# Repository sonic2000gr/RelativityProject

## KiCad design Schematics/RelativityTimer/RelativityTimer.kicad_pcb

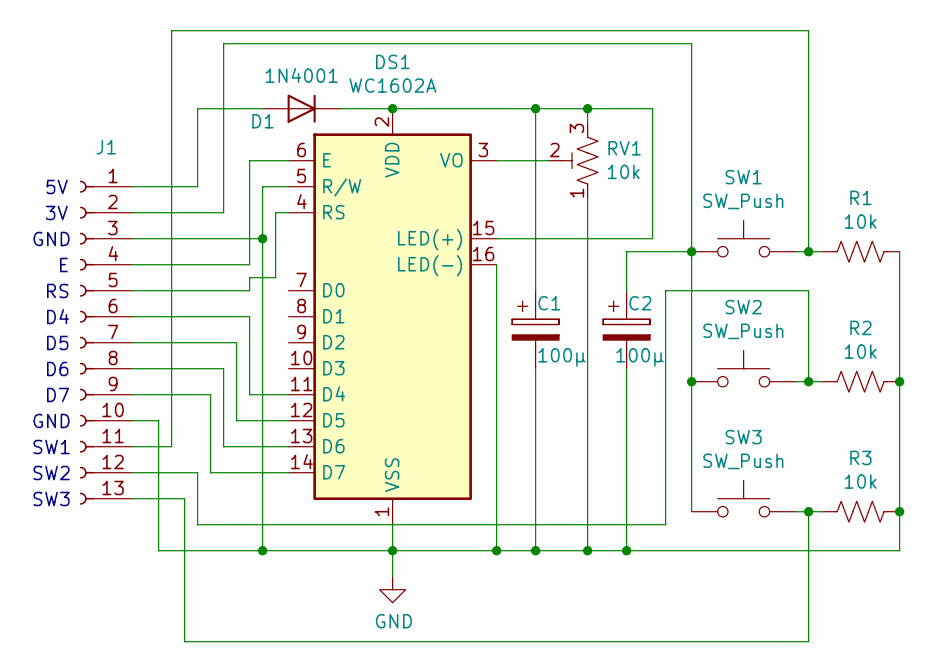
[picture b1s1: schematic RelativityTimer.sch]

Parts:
C1, C2: 100μ; CP_Radial_D8.0mm_P3.50mm
D1: 1N4001; D_DO-41_SOD81_P10.16mm_Horizontal
DS1: WC1602A
J1: Conn_01x12_Female; PinHeader_1x13_P2.54mm_Vertical
R1, R2, R3: 10k; R_Axial_DIN0207_L6.3mm_D2.5mm_P10.16mm_Horizontal
RV1: 10k; Potentiometer_ACP_CA9-H2,5_Horizontal
SW1, SW2, SW3: SW_Push; SW_PUSH_6mm_H4.3mm

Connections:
GND: C1.2, C2.2, DS1.1 (VSS), DS1.5 (R/W), DS1.16 (LED(-)), J1.3, J1.10, R1.1, R2.1, R3.1, RV1.1
unnamed: C1.1, D1.1 (K), DS1.2 (VDD), DS1.15 (LED(+)), RV1.3
unnamed: C2.1, J1.2, SW1.1, SW2.1, SW3.1
unnamed: D1.2 (A), J1.1
unnamed: DS1.3 (VO), RV1.2
unnamed: DS1.4 (RS), J1.5
unnamed: DS1.6 (E), J1.4
unnamed: DS1.11 (D4), J1.6
unnamed: DS1.12 (D5), J1.7
unnamed: DS1.13 (D6), J1.8
unnamed: DS1.14 (D7), J1.9
unnamed: J1.11, R1.2, SW1.2
unnamed: J1.12, R2.2, SW2.2
unnamed: J1.13, R3.2, SW3.2

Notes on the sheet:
GND
SW1
SW2
SW3

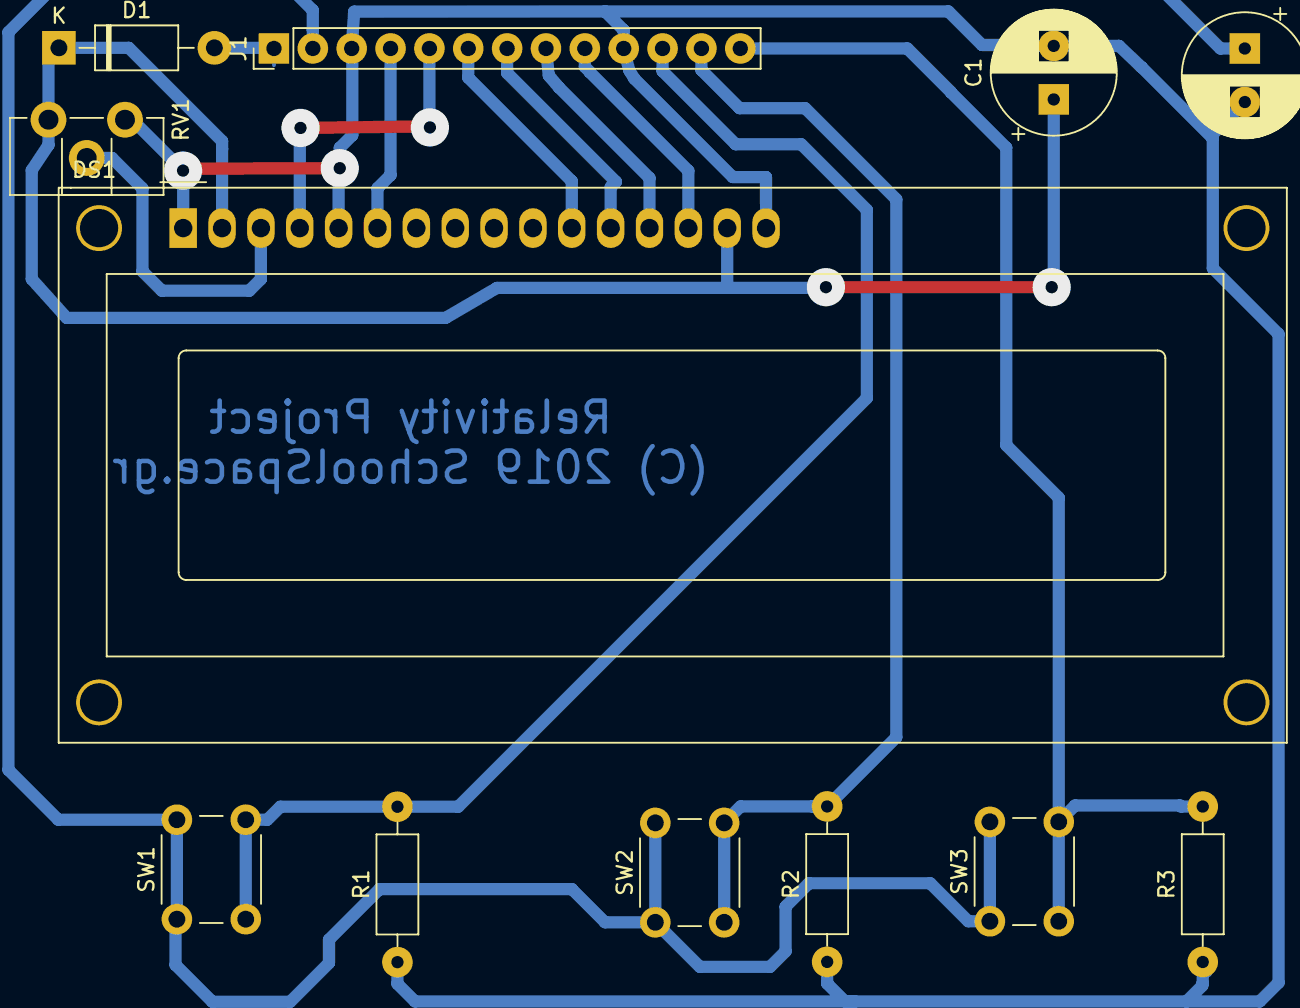
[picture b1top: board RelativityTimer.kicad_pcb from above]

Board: 2 copper layers, 12 parts (0 on the bottom side), 14 nets.

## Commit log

2019-02-08 Add initial schematics for LCD board
2019-02-08 Improve the PCB a bit
2019-02-21 Minor changes to 1.0 printed board
2019-02-21 Mirror copyright message in PCB
2019-02-21 Add protection diode for LCD
2019-04-06 Add final version of RelativityTimer arduino sketch
2019-04-08 Add final arduino sketch for relativity scale
2019-04-10 Add relativity project presentation for exhibition

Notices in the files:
Schematics/RelativityTimer/RelativityTimer.kicad_pcb:
(C) 2019 SchoolSpace.gr
